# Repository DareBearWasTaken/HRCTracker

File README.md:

# Handheld Cadence Tracker

A responsive handheld walking and running cadence tracker built with an
ESP32-C5, an MPU9250-series inertial sensor, and a 128×64 SSD1306 OLED.

The tracker measures rhythmic handheld motion, filters out gravity and
orientation changes, validates step timing, and displays both the current and
average cadence in steps per minute (SPM). An LED provides immediate feedback
whenever a step is detected.

## Features

- 125 Hz accelerometer and gyroscope sampling
- Orientation-independent handheld motion detection
- Automatic stillness calibration at startup
- Adaptive accelerometer and gyroscope thresholds
- Hysteretic peak detection and false-motion rejection
- Rhythm locking for more reliable step validation
- Recovery from an occasional missed step impact
- Session step counter
- Average active cadence display
- Responsive current cadence display
- Immediate, non-blocking LED step indication
- OLED and sensor access coordinated to protect sample timing
- No button required

## Display

During tracking, the OLED shows:

- **AVG SPM:** Average cadence across accepted active step intervals
- **NOW:** Smoothed current cadence
- **STEPS:** Total confirmed and recovered steps
- **MOT:** Live motion-strength indicator
- **AVG CAD / AVG SEEK:** Whether a stable walking or running rhythm has been
  established

Pauses and rejected hand movements are not included in the average cadence.
The average remains available if rhythm lock is temporarily lost.

## Hardware

- ESP32-C5 development board
- MPU9250, MPU9255, or MPU6500 motion sensor
- 128×64 SSD1306 I²C OLED at address `0x3C` or `0x3D`
- Indicator LED
- 220–330 Ω LED resistor
- Jumper wires or a custom PCB

## Wiring

The firmware defaults to the original split-bus wiring below.

| Device | Signal | ESP32-C5 pin |
|---|---|---:|
| OLED | SDA | GPIO23 |
| OLED | SCL | GPIO24 |
| MPU | SDA | GPIO25 |
| MPU | SCL | GPIO26 |
| LED | Anode through 220–330 Ω resistor | GPIO2 |
| LED | Cathode | GND |

Connect the ESP32-C5, OLED, and MPU grounds together. Power each module using
the voltage supported by the specific breakout board being used.

The ESP32-C5 has one high-performance I²C controller that can be routed to the
arbitrary GPIO pins above. The firmware therefore locks the controller during
an OLED transfer, selects the OLED pins, transmits one frame, restores the MPU
pins, and releases the sensor task. The display refresh is limited to 2 FPS so
these interruptions remain short and infrequent.

## Firmware requirements

- Arduino IDE 2.x
- Espressif ESP32 Arduino core with ESP32-C5 support
- [Adafruit GFX Library](https://github.com/adafruit/Adafruit-GFX-Library)
- [Adafruit SSD1306](https://github.com/adafruit/Adafruit_SSD1306)

The MPU is configured directly through its registers. A separate MPU9250
Arduino library is not required.

## Installation

1. Install the Espressif ESP32 board package in Arduino IDE.
2. Install **Adafruit GFX Library** and **Adafruit SSD1306** using Library
   Manager.
3. Open [`cadence_tracker_screen_average.ino`](cadence_tracker_screen_average.ino).
4. Select **ESP32C5 Dev Module** as the board.
5. Select the correct serial port.
6. Compile and upload the sketch.

The firmware has been compile-tested with the following board identifier:

```text
esp32:esp32:esp32c5
```

## Using the tracker

1. Turn on or reset the tracker.
2. Confirm that the LED flashes three times during its startup test.
3. Hold the tracker completely still while the calibration screen reaches
   100%.
4. Hold the tracker naturally and begin walking or running.
5. The first valid motion flashes the LED immediately.
6. Two plausibly timed detections establish rhythm lock and begin the cadence
   display.

If the device moves repeatedly during calibration, the stable calibration
window restarts automatically.

## How cadence is calculated

The accelerometer magnitude is used so detection does not depend on the
orientation of the device. A slow baseline removes gravity and gradual hand
orientation changes. Filtered gyroscope motion then corroborates the
acceleration signal.

Candidate peaks must satisfy motion-strength, timing, and refractory-period
checks. After rhythm lock:

- Recent accepted intervals produce the responsive **NOW** cadence.
- All accepted active intervals produce the session **AVG SPM** cadence.
- A gap near two expected periods can recover one weak or missed impact.
- Pauses and rejected peaks do not lower the active-cadence average.

## Configuration and tuning

The default values are intended as a balanced starting point for handheld
walking and running. Test the tracker before changing them.

Useful constants near the top of the sketch include:

| Constant | Purpose |
|---|---|
| `SENSOR_PERIOD_MS` | Sensor sampling interval |
| `DISPLAY_PERIOD_MS` | OLED refresh interval |
| `MIN_STEP_INTERVAL_MS` | Maximum allowed cadence |
| `MAX_STEP_INTERVAL_MS` | Minimum cadence used while seeking rhythm |
| `PEAK_TRIGGER_SCORE` | Motion strength required to open a candidate peak |
| `PEAK_RELEASE_SCORE` | Hysteresis level used to finish a peak |

For missed real steps, reduce the lower acceleration-threshold clamp slightly.
For false steps caused by ordinary hand movement, increase
`PEAK_TRIGGER_SCORE` in small increments. Change only one value at a time and
test at multiple walking and running speeds.

## KiCad hardware files

KiCad design files for the custom cadence-tracker hardware will be added to
this repository. The planned hardware release includes:

- KiCad project file (`.kicad_pro`)
- Schematic (`.kicad_sch`)
- PCB layout (`.kicad_pcb`)
- Component and connector details
- Fabrication outputs and a bill of materials when available

A recommended repository location is:

```text
hardware/
└── kicad/
    ├── handheld_cadence_tracker.kicad_pro
    ├── handheld_cadence_tracker.kicad_sch
    └── handheld_cadence_tracker.kicad_pcb
```

Until those files are uploaded, the wiring table above is the reference for
building the prototype.

## Suggested repository structure

```text
.
├── cadence_tracker_screen_average.ino
├── README.md
├── hardware/
│   └── kicad/                 # KiCad files will be added here
└── docs/                      # Optional photos and build notes
```

## Troubleshooting

### OLED remains blank

- Confirm SDA is connected to GPIO23 and SCL to GPIO24.
- Confirm the OLED is an I²C SSD1306 display.
- Check whether its address is `0x3C` or `0x3D`; the firmware tries both.
- Verify common ground and the module's supply voltage.
- Open Serial Monitor at 115200 baud and check for `OLED not found`.

### Tracker stays on the calibration screen

Place it on a stable surface or hold it completely still. Sustained movement
intentionally restarts calibration.

### Cadence remains blank

The tracker needs two plausibly timed motion peaks before rhythm lock. Confirm
that the LED responds while walking naturally.

### MPU initialization fails

- Confirm SDA is connected to GPIO25 and SCL to GPIO26.
- Check power and ground.
- The firmware checks MPU addresses `0x68` and `0x69` automatically.

No license has been selected yet. Add a `LICENSE` file before distributing or
accepting contributions if you want to define reuse terms explicitly.

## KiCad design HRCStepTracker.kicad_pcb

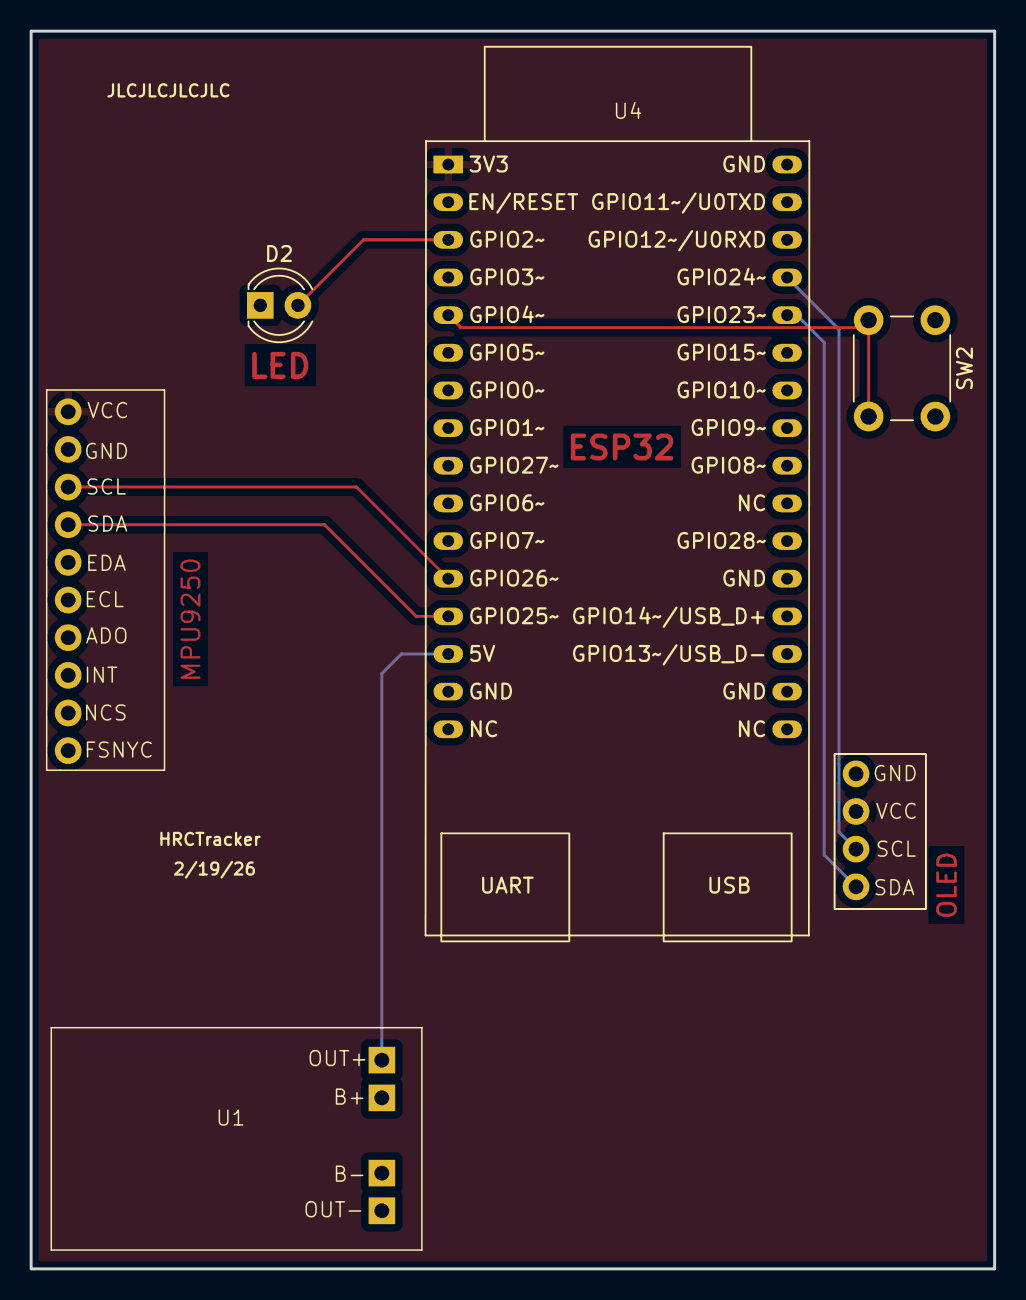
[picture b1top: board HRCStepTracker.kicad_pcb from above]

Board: 4 copper layers, 65.0 x 83.5 mm, 6 parts (0 on the bottom side), 9 nets.

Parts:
D2: LED; LED_D4.0mm
SW2: SW_Push; SW_PUSH_6mm_H4.3mm
U1: TP4056
U4: ESP32-C5-DevKitC-1
U5: SSD1306
U6: MPU6500

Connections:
+3V3: U4.1 (3V3), U5.2 (VCC), U6.1 (VCC)
+5V: U1.1 (OUT+), U4.14 (5V)
GND: D2.1 (K), SW2.1, U1.4 (OUT-), U4.15 (GND), U4.18 (GND), U4.21 (GND), U4.32 (GND), U5.1 (GND), U6.2 (GND)
unnamed: D2.2 (A), U4.3 (GPIO2/MTMS)
unnamed: SW2.2, U4.5 (GPIO4/MTCK)
unnamed: U4.28 (GPIO23), U5.4 (SDA)
unnamed: U4.29 (GPIO24), U5.3 (SCL)
unnamed: U4.13 (GPIO25), U6.4 (SDA)
unnamed: U4.12 (GPIO26), U6.3 (SCL)

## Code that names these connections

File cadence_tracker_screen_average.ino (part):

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// ============================================================
//
// Default wiring (matches the original tracker):
//   OLED SDA -> GPIO23      OLED SCL -> GPIO24
//   MPU SDA  -> GPIO25      MPU SCL  -> GPIO26
//   LED +    -> GPIO2 through a 220-330 ohm resistor
//   LED -    -> GND
//
// ESP32-C5 has only one high-performance I2C controller that can use
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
